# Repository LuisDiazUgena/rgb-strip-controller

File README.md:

# rgb-strip-controller

Rgb strip controller for WS2812 led stripes like Adafruit Neopixel.

Please check out <a href="#updates">updates</a> below.

# Hardware

It uses an Attiny 84 to run the code and a HC-06 bluetooth module to communicate with Bluetooth with an [app](https://github.com/LuisDiazUgena/Hack-A-Lamp/).

You can find a production board in [Hardware/For Manufacturing folder](https://github.com/LuisDiazUgena/rgb-strip-controller/tree/master/Hardware/For%20manufacturing)

The board it's designed to be milled with [Cyclone](https://store.bq.com/es/cyclone), an open source CNC(Project [here](https://github.com/carlosgs/Cyclone-PCB-Factory)).

# Software

I've created a sketch that uses [Neopixel library by Adafruit](https://github.com/adafruit/Adafruit_NeoPixel) to control Neopixel strip.

You can find it under [rgb-strip-controller](https://github.com/LuisDiazUgena/rgb-strip-controller/tree/master/rgb-strip-controller) folder

## Usage

Download the project and move .proto file to your smartphone (**recommended**) or tablet.

You can also open Protocoder file on your computer and copy it into an empty project on Protocoder web IDE.

**If your Arduino/Arduino cloned board/board doesn't have a Bluetooth module, you should connect a BT module and handle to receive data over BT-Serial.**

Upload *rgb-strip-controller.ino* file to your Arduino board.

Install protocoder apk on your device and then, with a file explorer, open *projects_Hack-a-lamp.proto* file with protocoder. Then run it on your device.

You **must** first pair your BT board or module to your device with bluetooth settings.

On protocoder interface click on Connect to Bluetooth and choose your board, wait until both BTs are connected and move the sliders, then click on Send to change the color.

**Auto send feature**: Use this is you want Protocoder send data color as you modify it. Using this feature provides a almost real time experience.

**On/Off switch**: When it's turned on, the color is set to white. When it's turned off, the color is set to black.

###<a name="updates">Updates</a>

**26-01-2016**

1. Recieved pcb boards and testing. It works!

**28-12-2015**

1. Finished sketch and tested on breadboard
2. Finished PCB layout
3. Created Gerbers
4. Created Gcodes

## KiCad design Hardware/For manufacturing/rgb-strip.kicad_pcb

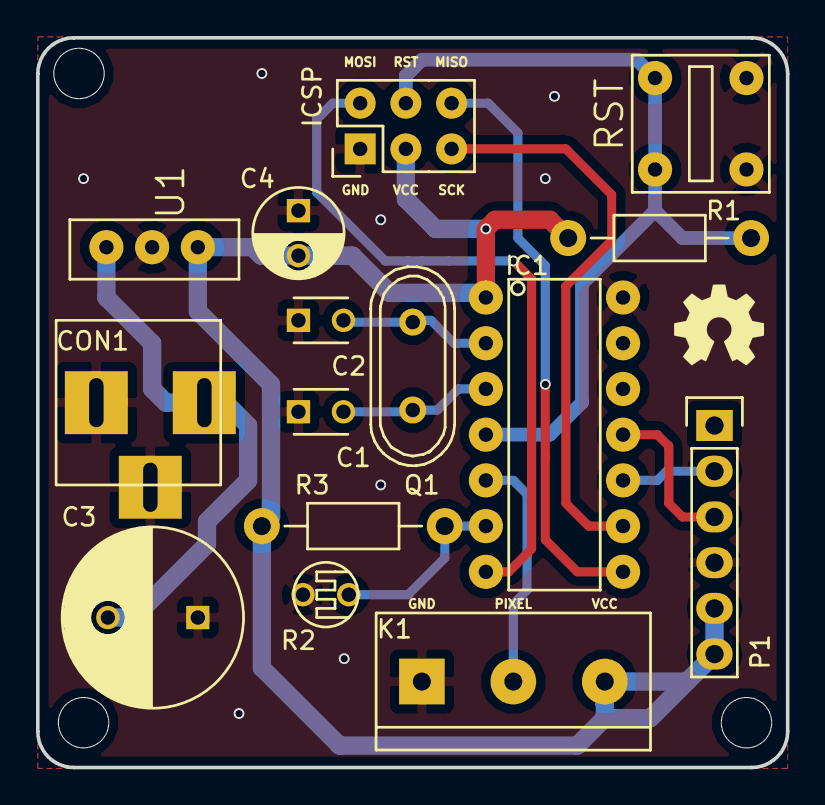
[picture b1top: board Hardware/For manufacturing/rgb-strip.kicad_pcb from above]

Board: 2 copper layers, 41.7 x 40.5 mm, 15 parts (0 on the bottom side), 13 nets.

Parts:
C1, C2: 22pF; C_Disc_D3_P2.5
C3: 100uF; C_Radial_D10_L13_P5
C4: 10uF; C_Radial_D5_L6_P2.5
CON1: BARREL_JACK
IC1: ATTINY84-P; Attiny24-54-84
ICSP: ICSP; Pin_Header_Straight_2x03
K1: CONN_3_V; bornier3
P1: BT_Header-1x06; Pin_Header_Straight_1x06
Q1: HC49; Crystal_HC49-U_Vertical
R1, R3: 10K; Resistor_Horizontal_RM10mm
R2: LDR
RST: SW_PUSH
U1: 7805; LM7805

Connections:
BRX: IC1.10, P1.2
BTX: IC1.11, P1.3
GND: C1.1, C2.1, C3.1, C4.1, CON1.2, CON1.3, IC1.14, ICSP.6, K1.1, P1.4, R2.2, RST.2, U1.GND
LDR: IC1.6, R2.1, R3.2
MISO: IC1.8, ICSP.1
MOSI: IC1.7, ICSP.5
unnamed: C1.2, IC1.3, Q1.2
unnamed: C2.2, IC1.2, Q1.1
unnamed: C3.2, CON1.1, U1.VI
PixelPin: IC1.5, K1.2
RST: IC1.4, ICSP.3, R1.1, RST.1
SCK: IC1.9, ICSP.2
VCC: C4.2, IC1.1, ICSP.4, K1.3, P1.5, P1.6, R1.2, R3.1, U1.VO

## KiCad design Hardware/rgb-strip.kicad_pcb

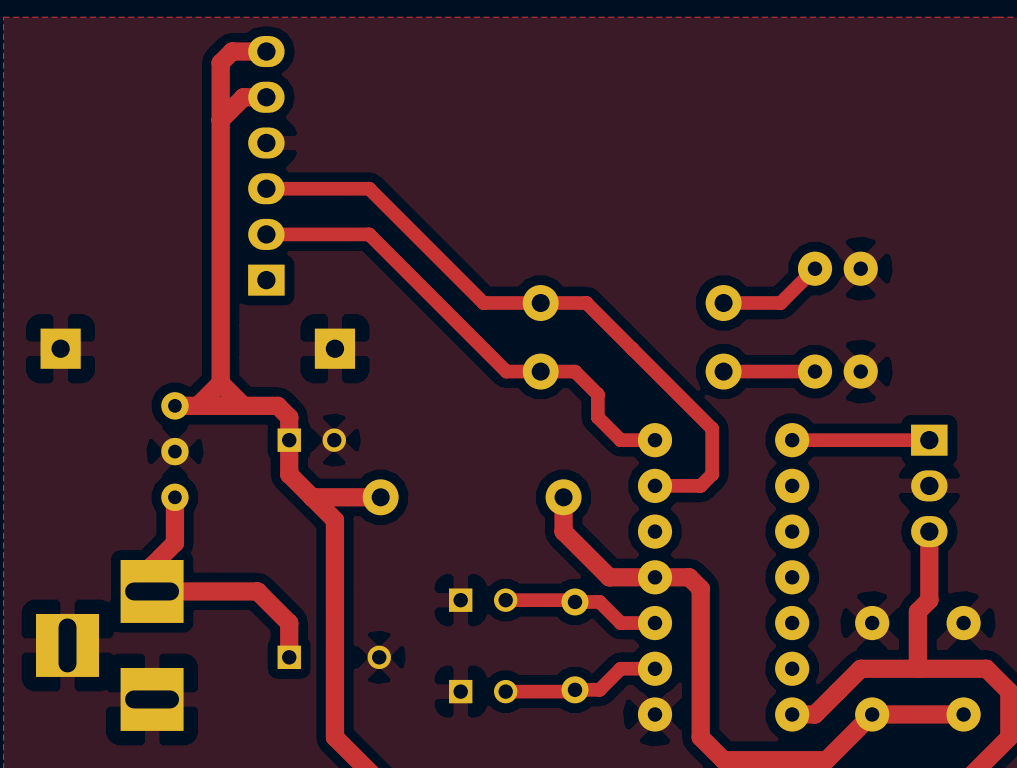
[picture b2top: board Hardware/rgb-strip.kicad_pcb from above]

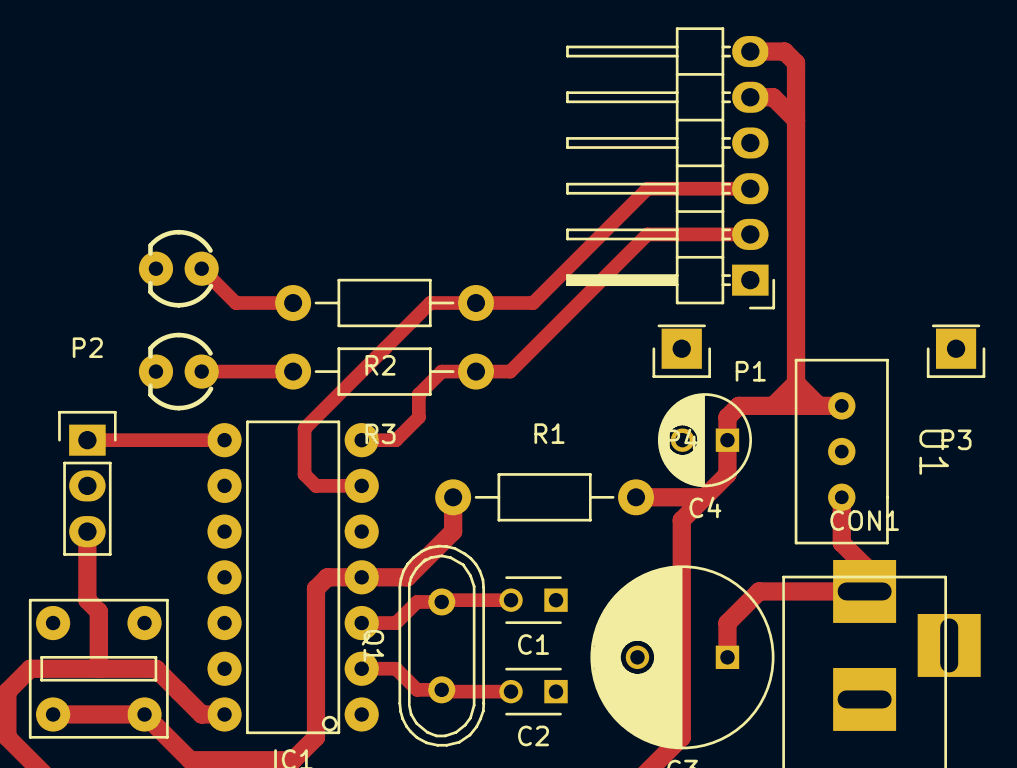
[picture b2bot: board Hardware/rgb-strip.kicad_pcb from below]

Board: 2 copper layers, 18 parts (18 on the bottom side), 11 nets.

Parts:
C1, C2: 22pF; C_Disc_D3_P2.5
C3: 100uF; C_Radial_D10_L13_P5
C4: 10uF; C_Radial_D5_L6_P2.5
CON1: BARREL_JACK
D1, D2: LED; LED-3MM
IC1: ATTINY84-P; Attiny24-54-84
P1: Bluetooth_Header; Pin_Header_Angled_1x06
P2: CONN_01X03; Pin_Header_Straight_1x03
P3, P4: CONN_01X01; Pin_Header_Straight_1x01
Q1: HC49; Crystal_HC49-U_Vertical
R1: 10K; Resistor_Horizontal_RM10mm
R2, R3: 330; Resistor_Horizontal_RM10mm
SW1: SW_PUSH
U1: LM7805

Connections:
BRX: IC1.7, P1.2, R3.1
BTX: IC1.6, P1.3, R2.1
GND: C1.1, C2.1, C3.2, C4.2, CON1.2, CON1.3, D1.1, D2.1, IC1.1, P1.4, P2.2, P3.1, P4.1, SW1.2, U1.GND
unnamed: C1.2, IC1.3, Q1.2
unnamed: C2.2, IC1.2, Q1.1
unnamed: C3.1, CON1.1, U1.VI
unnamed: D1.2, R2.2
unnamed: D2.2, R3.2
PixelPin: IC1.8, P2.1
RST: IC1.4, R1.1, SW1.1
VCC: C4.1, IC1.14, P1.5, P1.6, P2.3, R1.2, U1.VO

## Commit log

2015-11-25 Finished inital board design
2015-12-02 Created pcb layout
2015-12-02 initial commit for software
2015-12-02 pcb layout finished
2015-12-28 Added gcodes
2015-12-28 Added gerbers
2015-12-28 Finished board
2015-12-28 Finished sketch
2015-12-28 Added pcb-layout file
2015-12-28 Modified info about README
2015-12-28 Added size info
2015-12-28 Changed pixel number
2015-12-28 Added info about recent updates
2015-12-29 Moved to a folder
2015-12-30 Added fan support
2015-12-30 Created board for manufacturing, including better specs
2016-01-03 Finished board - minor improvements - Removed fan support
2016-01-03 Removed fan support - Started to work on ldr support
2016-01-03 Working on ldr support
2016-01-06 Improved design and updated gerbers
2016-01-10 Minor changes
2016-01-12 Bottom case created
2016-01-12 No changes, autofile created
2016-01-14 Started to work on a 3D printed case to hold the project
2016-01-14 improved code for ldr algorithm - not tested
2016-01-26 Added picture of the board
2016-01-26 fixed link-bug
